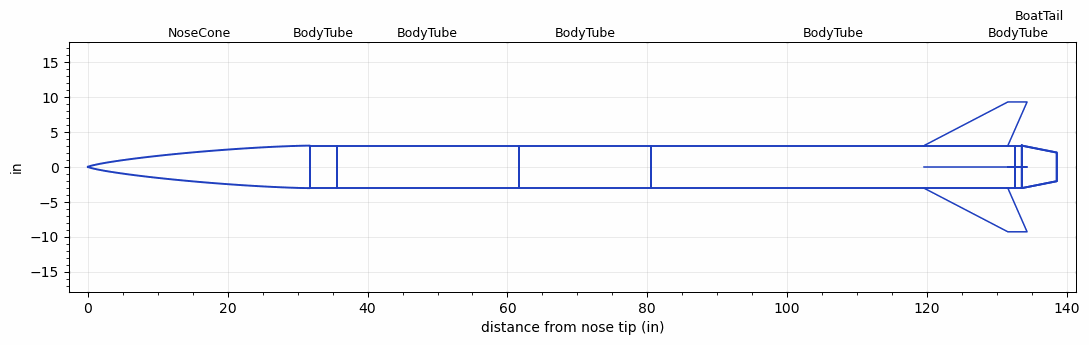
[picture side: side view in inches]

<RASAeroDocument>
 <FileVersion>2</FileVersion>
 <RocketDesign>
  <NoseCone>
   <Length>31.7499</Length>
   <Diameter>6.08</Diameter>
   <Shape>Von Karman Ogive</Shape>
   <Location>0</Location>
  </NoseCone>
  <BodyTube>
   <Length>3.85</Length>
   <Diameter>6.08</Diameter>
   <Location>31.7499</Location>
  </BodyTube>
  <BodyTube>
   <Length>25.9999</Length>
   <Diameter>6.08</Diameter>
   <Location>35.5999</Location>
  </BodyTube>
  <BodyTube>
   <Length>19</Length>
   <Diameter>6.08</Diameter>
   <Location>61.5998</Location>
  </BodyTube>
  <BodyTube>
   <Length>51.9999</Length>
   <Diameter>6.08</Diameter>
   <Location>80.5998</Location>
   <Fin>
    <Count>4</Count>
    <Chord>12</Chord>
    <Span>6.25</Span>
    <SweepDistance>12</SweepDistance>
    <TipChord>2.75</TipChord>
    <Thickness>0.28</Thickness>
    <LERadius>0.02</LERadius>
    <Location>13</Location>
    <AirfoilSection>Double Wedge</AirfoilSection>
    <FX1>3.75</FX1>
   </Fin>
  </BodyTube>
  <BodyTube>
   <Length>1</Length>
   <Diameter>6.08</Diameter>
   <Location>132.5997</Location>
   <BoattailLength>5</BoattailLength>
   <BoattailRearDiameter>4.1</BoattailRearDiameter>
  </BodyTube>
  <BoatTail>
   <Length>5</Length>
   <Diameter>6.08</Diameter>
   <RearDiameter>4.1</RearDiameter>
   <Location>133.5997</Location>
  </BoatTail>
  <Surface>Camouflage Paint</Surface>
  <ModifiedBarrowman>True</ModifiedBarrowman>
  <Turbulence>True</Turbulence>
  <UseBooster1>False</UseBooster1>
  <UseBooster2>False</UseBooster2>
  <Comments>Static bulkhead adjusted to match symmetry of dynamic bulkhead
</Comments>
 </RocketDesign>
 <LaunchSite>
  <Altitude>380</Altitude>
  <Pressure>28.81</Pressure>
  <RodAngle>6</RodAngle>
  <RodLength>17</RodLength>
  <Temperature>44.54</Temperature>
  <WindSpeed>7.33</WindSpeed>
 </LaunchSite>
 <Recovery>
  <Altitude1>0</Altitude1>
  <Altitude2>0</Altitude2>
  <DeviceType1>None</DeviceType1>
  <DeviceType2>None</DeviceType2>
  <Event1>False</Event1>
  <Event2>False</Event2>
  <Size1>0</Size1>
  <Size2>0</Size2>
  <EventType1>None</EventType1>
  <EventType2>None</EventType2>
  <CD1>0</CD1>
  <CD2>0</CD2>
 </Recovery>
 <SimulationList>
  <Simulation>
   <SustainerEngine>O5500X  (AT)</SustainerEngine>
   <SustainerLaunchWt>66.1</SustainerLaunchWt>
   <SustainerNozzleDiameter>2.72</SustainerNozzleDiameter>
   <SustainerCG>88.97</SustainerCG>
   <SustainerIgnitionDelay>0</SustainerIgnitionDelay>
   <Booster1SeparationDelay>0</Booster1SeparationDelay>
   <Booster1IgnitionDelay>0</Booster1IgnitionDelay>
   <IncludeBooster1>False</IncludeBooster1>
   <Booster2Delay>0</Booster2Delay>
   <IncludeBooster2>False</IncludeBooster2>
   <TimetoApogee>36.83982</TimetoApogee>
   <MaxAltitude>28793.8</MaxAltitude>
   <MaxVelocity>2288.26</MaxVelocity>
  </Simulation>
 </SimulationList>
</RASAeroDocument>
